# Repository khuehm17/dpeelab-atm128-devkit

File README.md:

# ATMEGA128 DEVELOPMENT KIT 
## Design by DPEE Lab
## #dpeelab-atm128-devkit
---
## Project description

An open-source AVR ATMega128 Development board KIT design with sample firmware

---
## Features
- 5V/3A Power supply
- ATMega128X compatibility
- USB Type C Serial UART
- JTAG/ISP Debug, programmer header
- Stackable with another module or extension board

---
## Hardware Revision 1.0

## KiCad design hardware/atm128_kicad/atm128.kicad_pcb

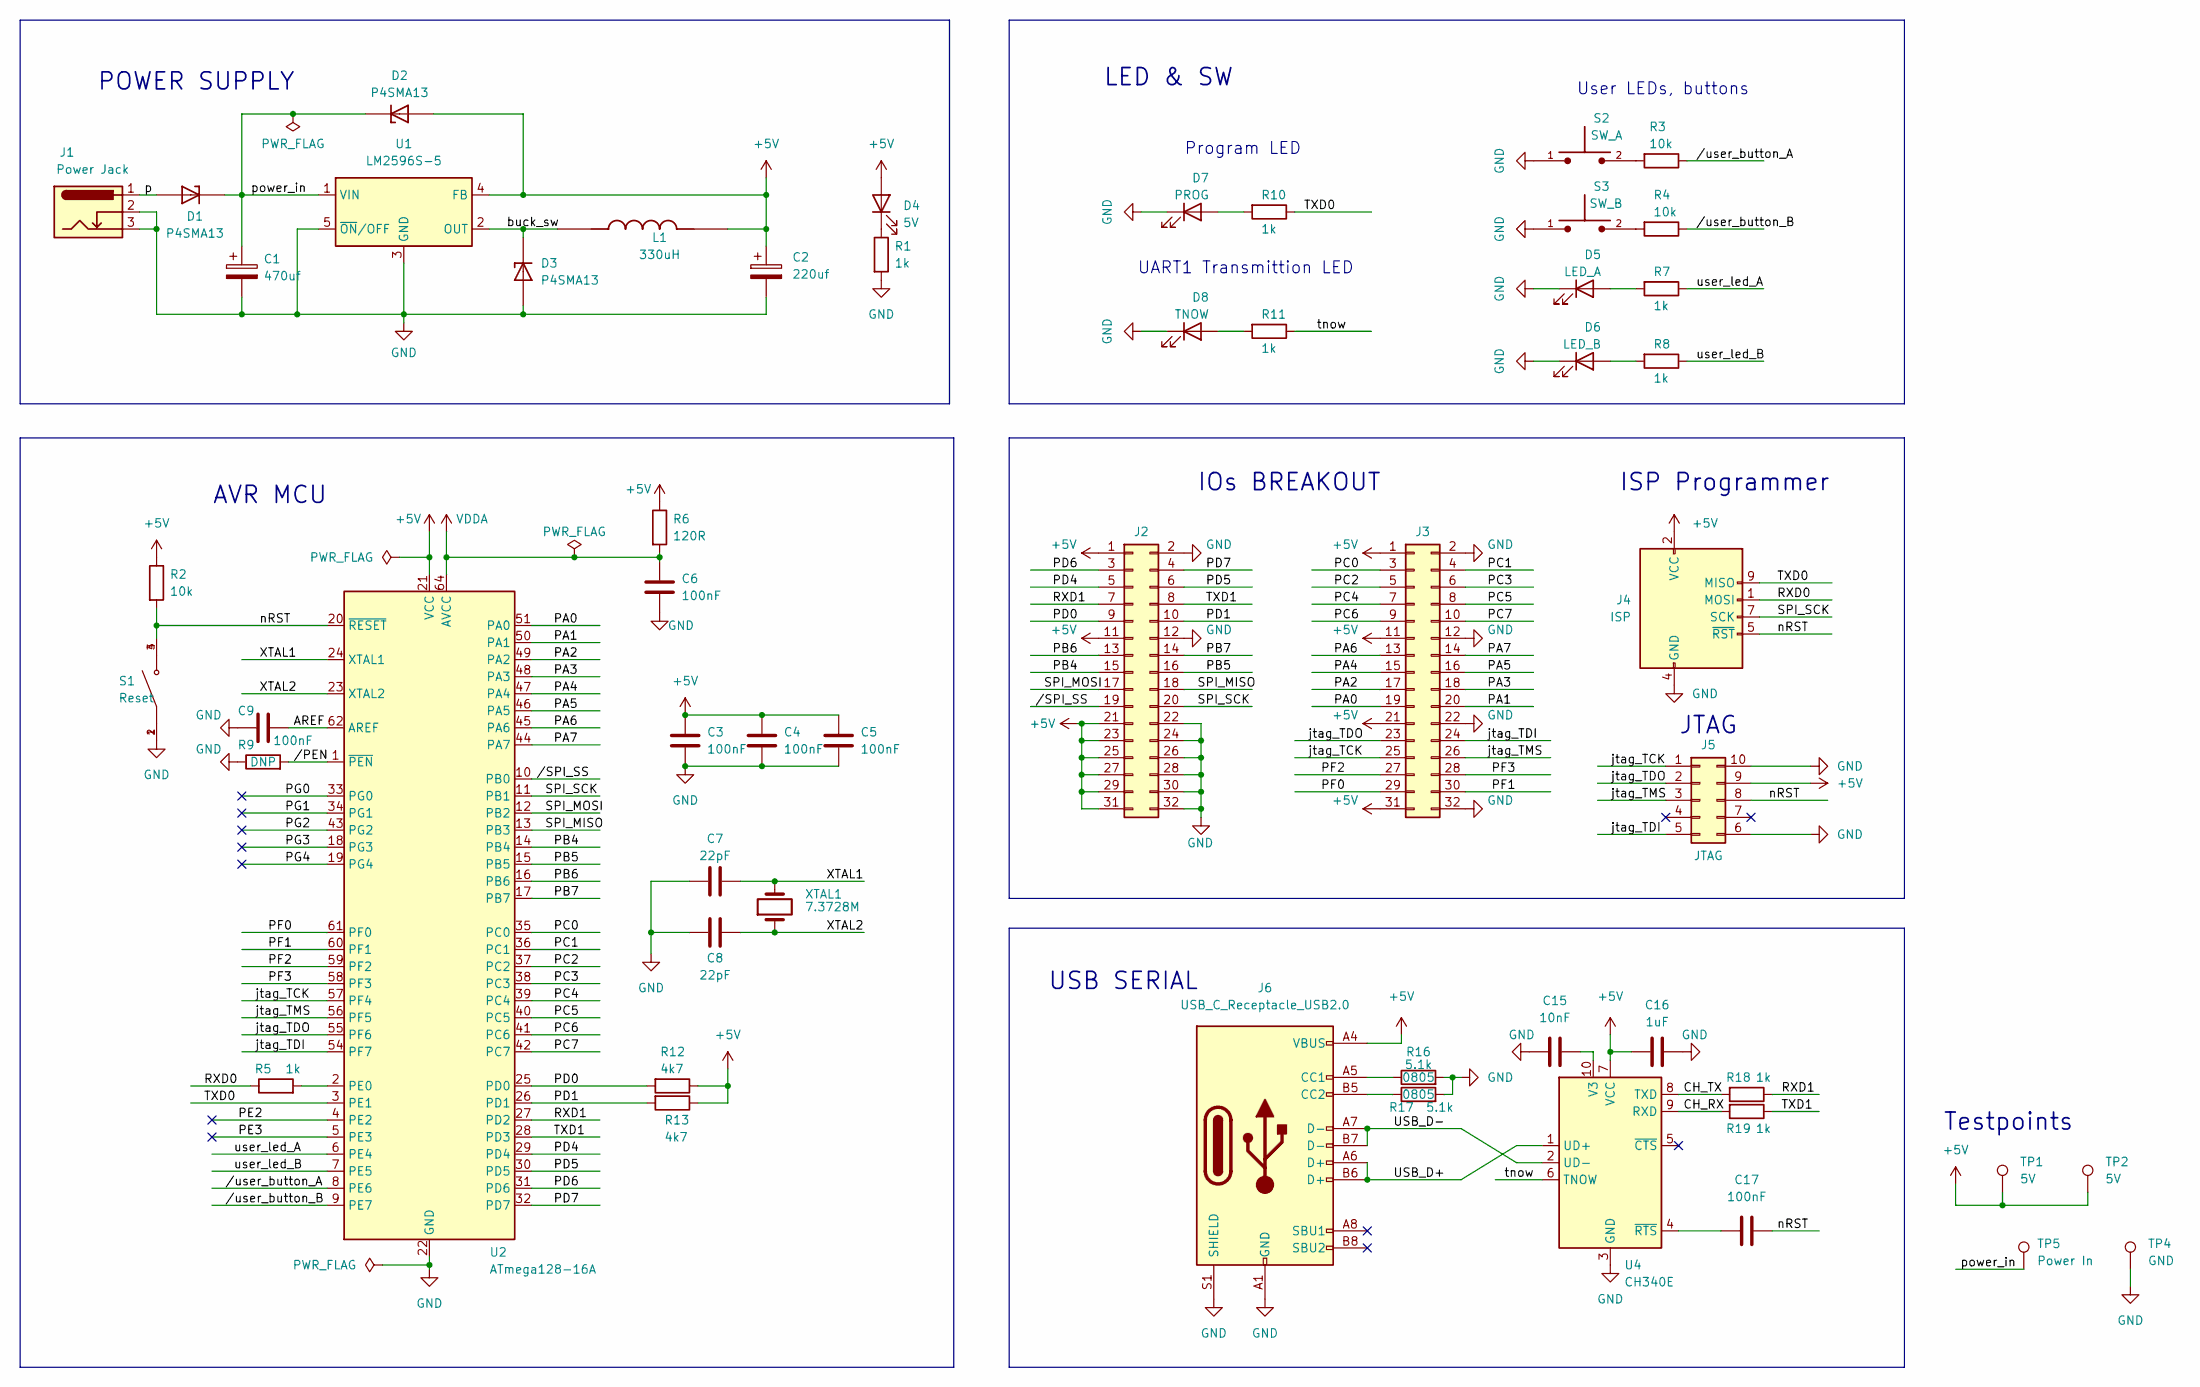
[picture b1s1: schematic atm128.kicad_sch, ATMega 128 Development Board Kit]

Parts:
C1: 470uf; CP_Elec_8x10.5
C2: 220uf; CP_Elec_6.3x7.7
C3, C4, C5, C6, C9, C17: 100nF; C_0805_2012Metric
C7, C8: 22pF; C_0805_2012Metric
C15: 10nF; C_0805_2012Metric
C16: 1uF; C_0805_2012Metric
D1, D2, D3: P4SMA13; DIOM4325X250N; PARTREV S2102
D4: 5V; LED_0805_2012Metric
D5: LED_A; LED_0805_2012Metric
D6: LED_B; LED_0805_2012Metric
D7: PROG; LED_0805_2012Metric
D8: TNOW; LED_0805_2012Metric
J1: Power Jack; BarrelJack_GCT_DCJ200-10-A_Horizontal
J2, J3: Conn_02x16_Odd_Even; PinHeader_2x16_P2.54mm_Vertical
J4: ISP; IDC-Header_2x05_P2.54mm_Vertical
J5: JTAG; PinHeader_2x05_P1.27mm_Vertical
J6: USB_C_Receptacle_USB2.0; USB_C_Receptacle_HRO_TYPE-C-31-M-12
L1: 330uH; IND_B1047AS-331M=P3; PARTREV N/A
R1, R5, R7, R8, R10, R11, R18, R19: 1k; R_0805_2012Metric
R2, R3, R4: 10k; R_0805_2012Metric
R6: 120R; R_0805_2012Metric
R9: DNP; R_0603_1608Metric
R12, R13: 4k7; R_0805_2012Metric
R16, R17: 5.1k; R_0805_2012Metric
S1: Reset; SW_4-1437565-9
S2: SW_A; SW_TL1015AF160QG; PARTREV F
S3: SW_B; SW_TL1015AF160QG; PARTREV F
TP1, TP2: 5V; TestPoint_Pad_D1.0mm
TP4: GND; TestPoint_Pad_D1.0mm
TP5: Power In; TestPoint_Pad_D1.0mm
U1: LM2596S-5; TO-263-5_TabPin3
U2: ATmega128-16A; TQFP-64_14x14mm_P0.8mm
U4: CH340E; MSOP-10_3x3mm_P0.5mm
XTAL1: 7.3728M; Crystal_SMD_HC49-SD

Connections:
+5V: C2.1, C3.1, C4.1, C5.1, C16.2, D2.A, D4.2 (A), J2.1, J2.11, J2.21, J2.23, J2.25, J2.27, J2.29, J2.31, J3.1, J3.11, J3.21, J3.31, J4.2 (VCC), J5.9, J6.A4 (VBUS), J6.A9 (VBUS), J6.B4 (VBUS), J6.B9 (VBUS), L1.2, R2.1, R6.1, R12.1, R13.1, TP1.1, TP2.1, U1.4 (FB), U2.21 (VCC), U2.52 (VCC), U4.7 (VCC)
/AREF: C9.2, U2.62 (AREF)
/CH_RX: R19.2, U4.9 (RXD)
/CH_TX: R18.2, U4.8 (TXD)
/PA0: J3.19, U2.51 (PA0)
/PA1: J3.20, U2.50 (PA1)
/PA2: J3.17, U2.49 (PA2)
/PA3: J3.18, U2.48 (PA3)
/PA4: J3.15, U2.47 (PA4)
/PA5: J3.16, U2.46 (PA5)
/PA6: J3.13, U2.45 (PA6)
/PA7: J3.14, U2.44 (PA7)
/PB4: J2.15, U2.14 (PB4)
/PB5: J2.16, U2.15 (PB5)
/PB6: J2.13, U2.16 (PB6)
/PB7: J2.14, U2.17 (PB7)
/PC0: J3.3, U2.35 (PC0)
/PC1: J3.4, U2.36 (PC1)
/PC2: J3.5, U2.37 (PC2)
/PC3: J3.6, U2.38 (PC3)
/PC4: J3.7, U2.39 (PC4)
/PC5: J3.8, U2.40 (PC5)
/PC6: J3.9, U2.41 (PC6)
/PC7: J3.10, U2.42 (PC7)
/PD0: J2.9, R12.2, U2.25 (PD0)
/PD1: J2.10, R13.2, U2.26 (PD1)
/PD4: J2.5, U2.29 (PD4)
/PD5: J2.6, U2.30 (PD5)
/PD6: J2.3, U2.31 (PD6)
/PD7: J2.4, U2.32 (PD7)
/PE2: U2.4 (PE2)
/PE3: U2.5 (PE3)
/PF0: J3.29, U2.61 (PF0)
/PF1: J3.30, U2.60 (PF1)
/PF2: J3.27, U2.59 (PF2)
/PF3: J3.28, U2.58 (PF3)
/PG0: U2.33 (PG0)
/PG1: U2.34 (PG1)
/PG2: U2.43 (PG2)
/PG3: U2.18 (PG3)
/PG4: U2.19 (PG4)
/RXD0: J4.1 (MOSI), R5.1
/RXD1: J2.7, R18.1, U2.27 (PD2)
/SPI_MISO: J2.18, U2.13 (PB3)
/SPI_MOSI: J2.17, U2.12 (PB2)
/SPI_SCK: J2.20, J4.7 (SCK), U2.11 (PB1)
/TXD0: J4.9 (MISO), R10.1, U2.3 (PE1)
/TXD1: J2.8, R19.1, U2.28 (PD3)
/USB_D+: J6.A6 (D+), J6.B6 (D+), U4.1 (UD+)
/USB_D-: J6.A7 (D-), J6.B7 (D-), U4.2 (UD-)
/XTAL1: C7.2, U2.24 (XTAL1), XTAL1.2
/XTAL2: C8.2, U2.23 (XTAL2), XTAL1.1
/buck_sw: D3.C, L1.1, U1.2 (OUT)
/jtag_TCK: J3.25, J5.1, U2.57 (PF4)
/jtag_TDI: J3.24, J5.5, U2.54 (PF7)
/jtag_TDO: J3.23, J5.2, U2.55 (PF6)
/jtag_TMS: J3.26, J5.3, U2.56 (PF5)
/nRST: C17.2, J4.5 (~RST), J5.8, R2.2, S1.3, S1.4, U2.20 (~RESET)
/p: D1.A, J1.1
/power_in: C1.1, D1.C, D2.C, TP5.1, U1.1 (VIN)
/tnow: R11.1, U4.6 (TNOW)
/user_led_A: R7.1, U2.6 (PE4)
/user_led_B: R8.1, U2.7 (PE5)
//PEN: R9.2, U2.1 (~PEN)
//SPI_SS: J2.19, U2.10 (PB0)
//user_button_A: R3.1, U2.8 (PE6)
//user_button_B: R4.1, U2.9 (PE7)
GND: C1.2, C2.2, C3.2, C4.2, C5.2, C6.2, C7.1, C8.1, C9.1, C15.1, C16.1, D3.A, D5.1 (K), D6.1 (K), D7.1 (K), D8.1 (K), J1.2, J1.3, J2.2, J2.12, J2.22, J2.24, J2.26, J2.28, J2.30, J2.32, J3.2, J3.12, J3.22, J3.32, J4.4 (GND), J4.6 (GND), J4.8 (GND), J4.10 (GND), J5.6, J5.10, J6.A1 (GND), J6.A12 (GND), J6.B1 (GND), J6.B12 (GND), J6.S1 (SHIELD), R1.2, R9.1, R16.2, R17.2, S1.1, S1.2, S2.1, S3.1, TP4.1, U1.3 (GND), U1.5 (~ON/OFF), U2.22 (GND), U2.53 (GND), U2.63 (GND), U4.3 (GND)
unnamed: C15.2, U4.10 (V3)
unnamed: C17.1, U4.4 (~RTS)
unnamed: D4.1 (K), R1.1
unnamed: D5.2 (A), R7.2
unnamed: D6.2 (A), R8.2
unnamed: D7.2 (A), R10.2
unnamed: D8.2 (A), R11.2
unnamed: J6.A5 (CC1), R16.1
unnamed: J6.B5 (CC2), R17.1
unnamed: R3.2, S2.2
unnamed: R4.2, S3.2
unnamed: R5.2, U2.2 (PE0)
VDDA: C6.1, R6.2, U2.64 (AVCC)

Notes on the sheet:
JTAG
USB SERIAL
User LEDs, buttons
LED & SW
UART1 Transmittion LED
Program LED
ISP Programmer
AVR MCU
POWER SUPPLY
Testpoints
IOs BREAKOUT

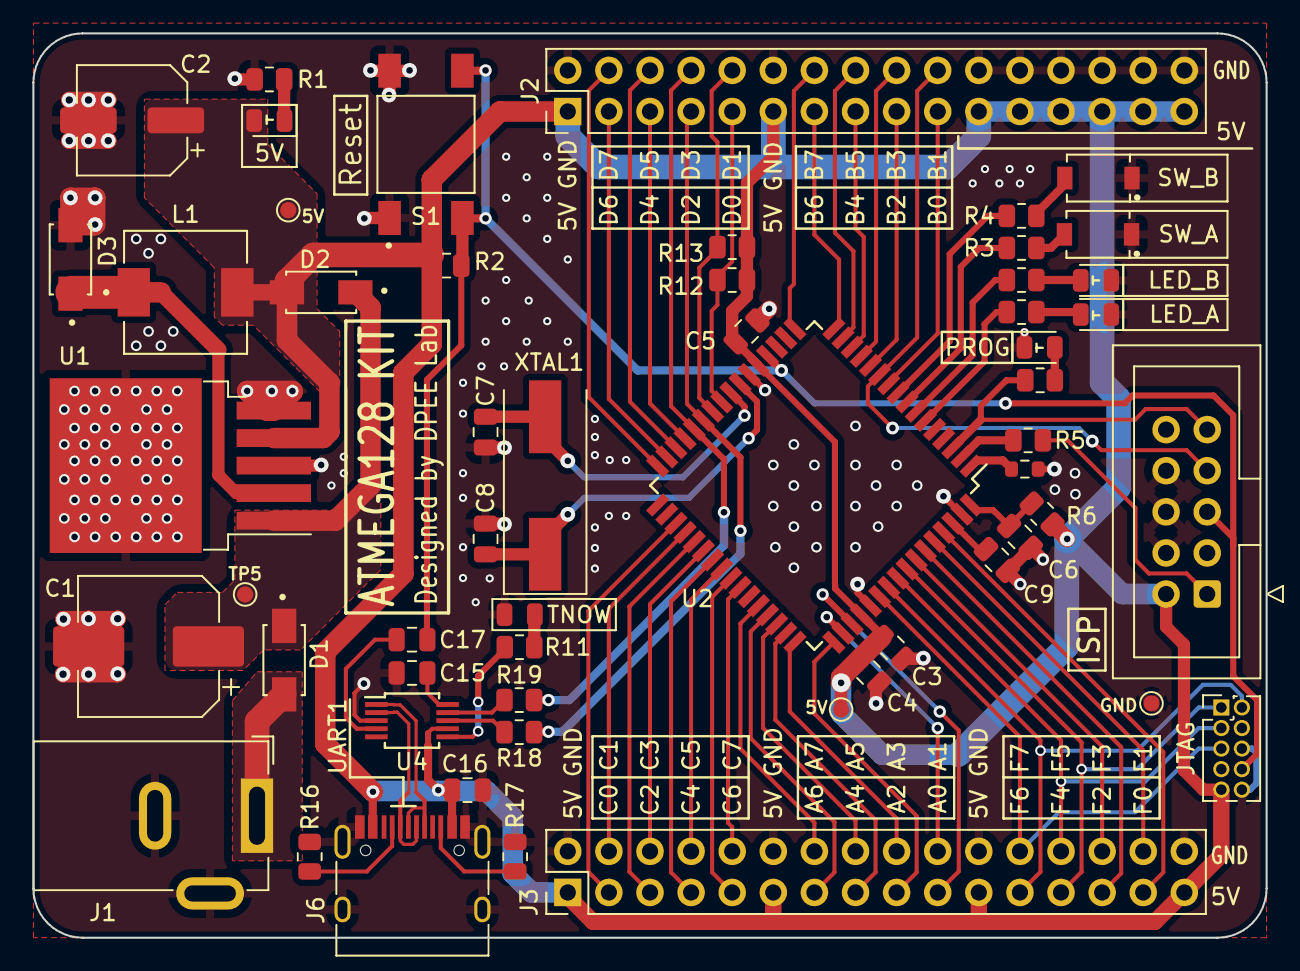
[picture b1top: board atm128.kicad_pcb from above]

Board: 2 copper layers, 76.2 x 55.9 mm, 55 parts (0 on the bottom side), 74 nets.

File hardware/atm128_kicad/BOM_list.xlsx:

Id | Designator | Package | Quantity | Designation | Supplier and ref | Ready | Ordered
1 | J6 | USB_Micro-B_Molex-105017-0001 | 1 | USB_B_Mini | https://www.thegioiic.com/products/cong-usb-micro-b-2-0-dau-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 |  | v
2 | R4,R2,R3 | R_0805_2012Metric | 3 | 10k | https://www.thegioiic.com/products/dien-tro-10-kohm-0805-1 |  | v
3 | TP1,TP2,TP3 | TestPoint_Pad_D1.0mm | 3 | 5V |  | v
4 | R10,R5,R14,R1,R7,R15,R11,R8 | R_0805_2012Metric | 8 | 1k | https://www.thegioiic.com/products/dien-tro-1-kohm-0805-5- | v
5 | R9 | R_0603_1608Metric | 1 | DNP | https://www.thegioiic.com/products/dien-tro-0-ohm-0603-5- |  | v
6 | C6 | C_0805_2012Metric | 1 | C |  |  | v
7 | R13,R12 | R_0805_2012Metric | 2 | 4k7 | https://www.thegioiic.com/products/dien-tro-4-7-kohm-0805-1- |  | v
8 | L1 | IND_B1047AS-331M=P3 | 1 | 330uH | https://www.thegioiic.com/products/cuon-cam-dan-smd-7345-331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 |  | v
9 | D7 | LED_0805_2012Metric | 1 | TX | https://www.thegioiic.com/products/led-xanh-la-0805-dan-smd-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 |  | v
10 | J1 | BarrelJack_GCT_DCJ200-10-A_Horizontal | 1 | Barrel_Jack_Switch_Pin3Ring
11 | C12 | C_0805_2012Metric | 1 | 10nF | https://www.thegioiic.com/products/tu-gom-0805-10nf-50v |  | v
12 | U2 | TQFP-64_14x14mm_P0.8mm | 1 | ATmega128-16A | https://www.thegioiic.com/products/atmega1281-16au |  | v
13 | J3,J2 | PinHeader_2x16_P2.54mm_Vertical | 2 | Conn_02x16_Odd_Even
14 | D4 | LED_0805_2012Metric | 1 | 5V | https://www.thegioiic.com/products/led-xanh-la-0805-dan-smd-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
15 | XTAL1 | Crystal_SMD_HC49-SD | 1 | 7.3728M | https://www.thegioiic.com/products/thach-anh-7-3728mhz-2-cha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 |  | v
16 | C13,C9 | C_0805_2012Metric | 2 | 100nF | https://www.thegioiic.com/products/tu-gom-0805-100nf-0-1uf-50v |  | v
17 | U1 | TO-263-5_TabPin3 | 1 | LM2596S-5 | https://www.thegioiic.com/products/lm2596s-5-0-ic-dieu-chinh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 |  | v
18 | D6 | LED_0805_2012Metric | 1 | LED_B | https://www.thegioiic.com/products/led-xanh-la-0805-dan-smd-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
19 | C8,C7 | C_0805_2012Metric | 2 | 22pF | https://www.thegioiic.com/products/tu-gom-0805-22pf-50v |  | v
20 | C4,C5,C3 | C_0805_2012Metric | 3 | 0.1uF | https://www.thegioiic.com/products/tu-gom-0805-100nf-0-1uf-50v
21 | D5 | LED_0805_2012Metric | 1 | LED_A | https://www.thegioiic.com/products/led-xanh-la-0805-dan-smd-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
22 | Y1 | Crystal_SMD_5032-2Pin_5.0x3.2mm | 1 | Crystal | https://www.thegioiic.com/products/thach-anh-12mhz-5032-2-ch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 |  | v
23 | C1 | CP_Elec_8x10.5 | 1 | 470uf | https://www.thegioiic.com/products/tu-nhom-smd-470uf-16v-8x10-5mm |  | v
24 | D1,D3,D2 | DIOM4325X250N | 3 | P4SMA13 | https://www.thegioiic.com/products/ss54-sma |  | v
25 | J5 | PinHeader_2x05_P1.27mm_Vertical | 1 | JTAG
26 | C10,C14,C11 | C_0805_2012Metric | 3 | 1uF | https://www.thegioiic.com/products/tu-gom-0805-1uf-25v |  | v
27 | TP4 | TestPoint_Pad_D1.0mm | 1 | GND
28 | J4 | PinHeader_1x06_P2.54mm_Vertical | 1 | ISP | https://www.thegioiic.com/products/hang-rao-duc-don-2-54mm-4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 |  | v
29 | C2 | CP_Elec_6.3x7.7 | 1 | 220uf | https://www.thegioiic.com/products/tu-nhom-smd-220uf-16v-6-3x7-7mm | v
30 | S3 | SW_TL1015AF160QG | 1 | SW_B | https://www.thegioiic.com/products/nut-nhan-3x4mm-cao-2-5mm-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 |  | v
31 | D8 | LED_0805_2012Metric | 1 | RX | https://www.thegioiic.com/products/led-xanh-la-0805-dan-smd-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
32 | S2 | SW_TL1015AF160QG | 1 | SW_A | https://www.thegioiic.com/products/nut-nhan-3x4mm-cao-2-5mm-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 |  | v
33 | S1 | SW_4-1437565-9 | 1 | RST | https://www.thegioiic.com/products/nut-nhan-6x6mm-cao-4-3mm-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 | v
34 | U3 | SOIC-16_3.9x9.9mm_P1.27mm | 1 | CH340G | https://www.thegioiic.com/products/ch340g |  | v
35 | R6 | R_0805_2012Metric | 1 | 120R | https://www.thegioiic.com/products/dien-tro-120-ohm-0805-5- |  | v

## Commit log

2022-06-14 feat[hw]: add hardware PCB design by Kicad prototype Rev0.0
2022-06-22 docs: update schematic and board mechanism rev1.0
2022-06-30 feat: update hw: USB_C, IDC ISP, CH340E
2022-06-30 feat: modify J2, J3 space to 2000mils
2022-06-30 feat: update schematic Rev1.0
2022-06-30 docs: update board mechanism for Rev1.0
2022-07-19 feat: add TNOW LED, complete review for rev1.0
2022-07-19 release: export pcb gerber for fab #rev1.0
2022-07-26 feat[fw]: add out-of-the-box-demo firmware
2022-07-26 feat: add BOM for PCB rev1.0
2022-07-27 docs: update project description and rev1.0 infor
2022-08-05 create AVR 128 AUTOSAR
2022-08-05 Create readme file
2022-08-06 update state
2022-08-06 Create folder ControlUnit attach source code
2022-08-06 Restruct folder
2022-08-06 fix bug function change state
2022-08-06 create udsdiag folder
2022-08-07 update header function
2022-08-10 update final source code
2022-08-14 update final
